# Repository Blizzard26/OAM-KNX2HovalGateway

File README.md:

# Hoval2KNXGateway

A KNX gateway for Hoval TopTronic systems, enabling integration between KNX home automation networks and Hoval CAN-based controllers.

It is a PlatformIO project and needs a working ETS 5.7 (or higher) installed on the same PC (at least for generating the required ETS files).

It uses some Modules from the OpenKNX project: OGM-Common, OFM-cnofigTransfer, OFM-FileTransferModule, OFM-LogicModule

## Description

This project implements a bridge between KNX protocol and Hoval's proprietary CAN-based communication protocol. It allows KNX devices to read and write parameters from Hoval TopTronic systems.

The gateway uses the Hoval Message Protocol over CAN bus at 50kbps, supporting both single and multi-part messages for comprehensive datapoint access.

## Supported Hardware

Currently supports

- Seeeduino XIAO RP2040 with a MCP2515 (and a support CAN Transceive, e.g. MCP2562). Make sure to electrically separate the KNX bus from the Hoval bus as the operate on different potentials.

## Software Requirements

- **PlatformIO**: For building and flashing the firmware
- **Git**: For cloning this repository
- **Arduino Framework**: Used via PlatformIO
- **Dependencies**:
  - KNX library (version 2.2.2+)
  - Seeed Arduino CAN library
  - Various OpenKNX modules

## Installation

1. Clone this repository and initialize submodules:
   ```bash
   git clone <repository-url>
   cd Hoval2KNXGateway
   git submodule update --init --recursive
   ```
   NOTE: In contrast to other OpenKNX Projects this project uses git submodule to pull in libraries instead of restore scripts and `dependencies.txt`.

2. Install PlatformIO if not already installed.

3. Install dependencies:
   ```bash
   pio lib install
   ```

## Building

Use the provided build scripts or PlatformIO directly:

### Development Build
```bash
scripts/Build-Release.ps1
```
Or use the VS Code task: `Build-Dev`

### Release Build
```bash
scripts/Build-Release.ps1 Release
```
Or use the VS Code task: `Build-Release`

### Configuration

- Configure KNX parameters using ETS (Engineering Tool Software)

### Monitoring

Connect to the serial port at 115200 baud for debug output and monitoring.

There are four new commands added:

- `hoval log message`: Log received and processed messages - header only.
- `hoval log messageData`: Log received and processed message - including (parsed) data.
- `hoval log filtered`: Log filtered message, i.e., messages not known to the decoder - header only.
- `hoval log filteredData`: Log filtered message - including raw data.

## Project Structure

- `src/`: Main source code
- `include/`: Header files and configuration
- `lib/`: Library dependencies and modules
- `docs/`: Protocol documentation (Hoval.adoc)
- `schematics/`: Hardware schematics in KiCad format
- `scripts/`: Build and utility scripts
- `test/`: Test files

## Documentation

Detailed protocol documentation is available in `docs/Hoval.adoc`, including:
- Message structure and addressing
- Function codes and datapoints
- Communication flow examples

## Contributing

1. Fork the repository
2. Create a feature branch
3. Make your changes
4. Test thoroughly
5. Submit a pull request

## License

GNU General Public License v3.0

## Support

For issues and questions:
- Check the debug logs via serial output
- Refer to the protocol documentation
- Ensure proper hardware connections

## Disclaimer

This software is provided as-is. Ensure compatibility with your specific Hoval system and KNX installation. Always backup configurations before making changes.

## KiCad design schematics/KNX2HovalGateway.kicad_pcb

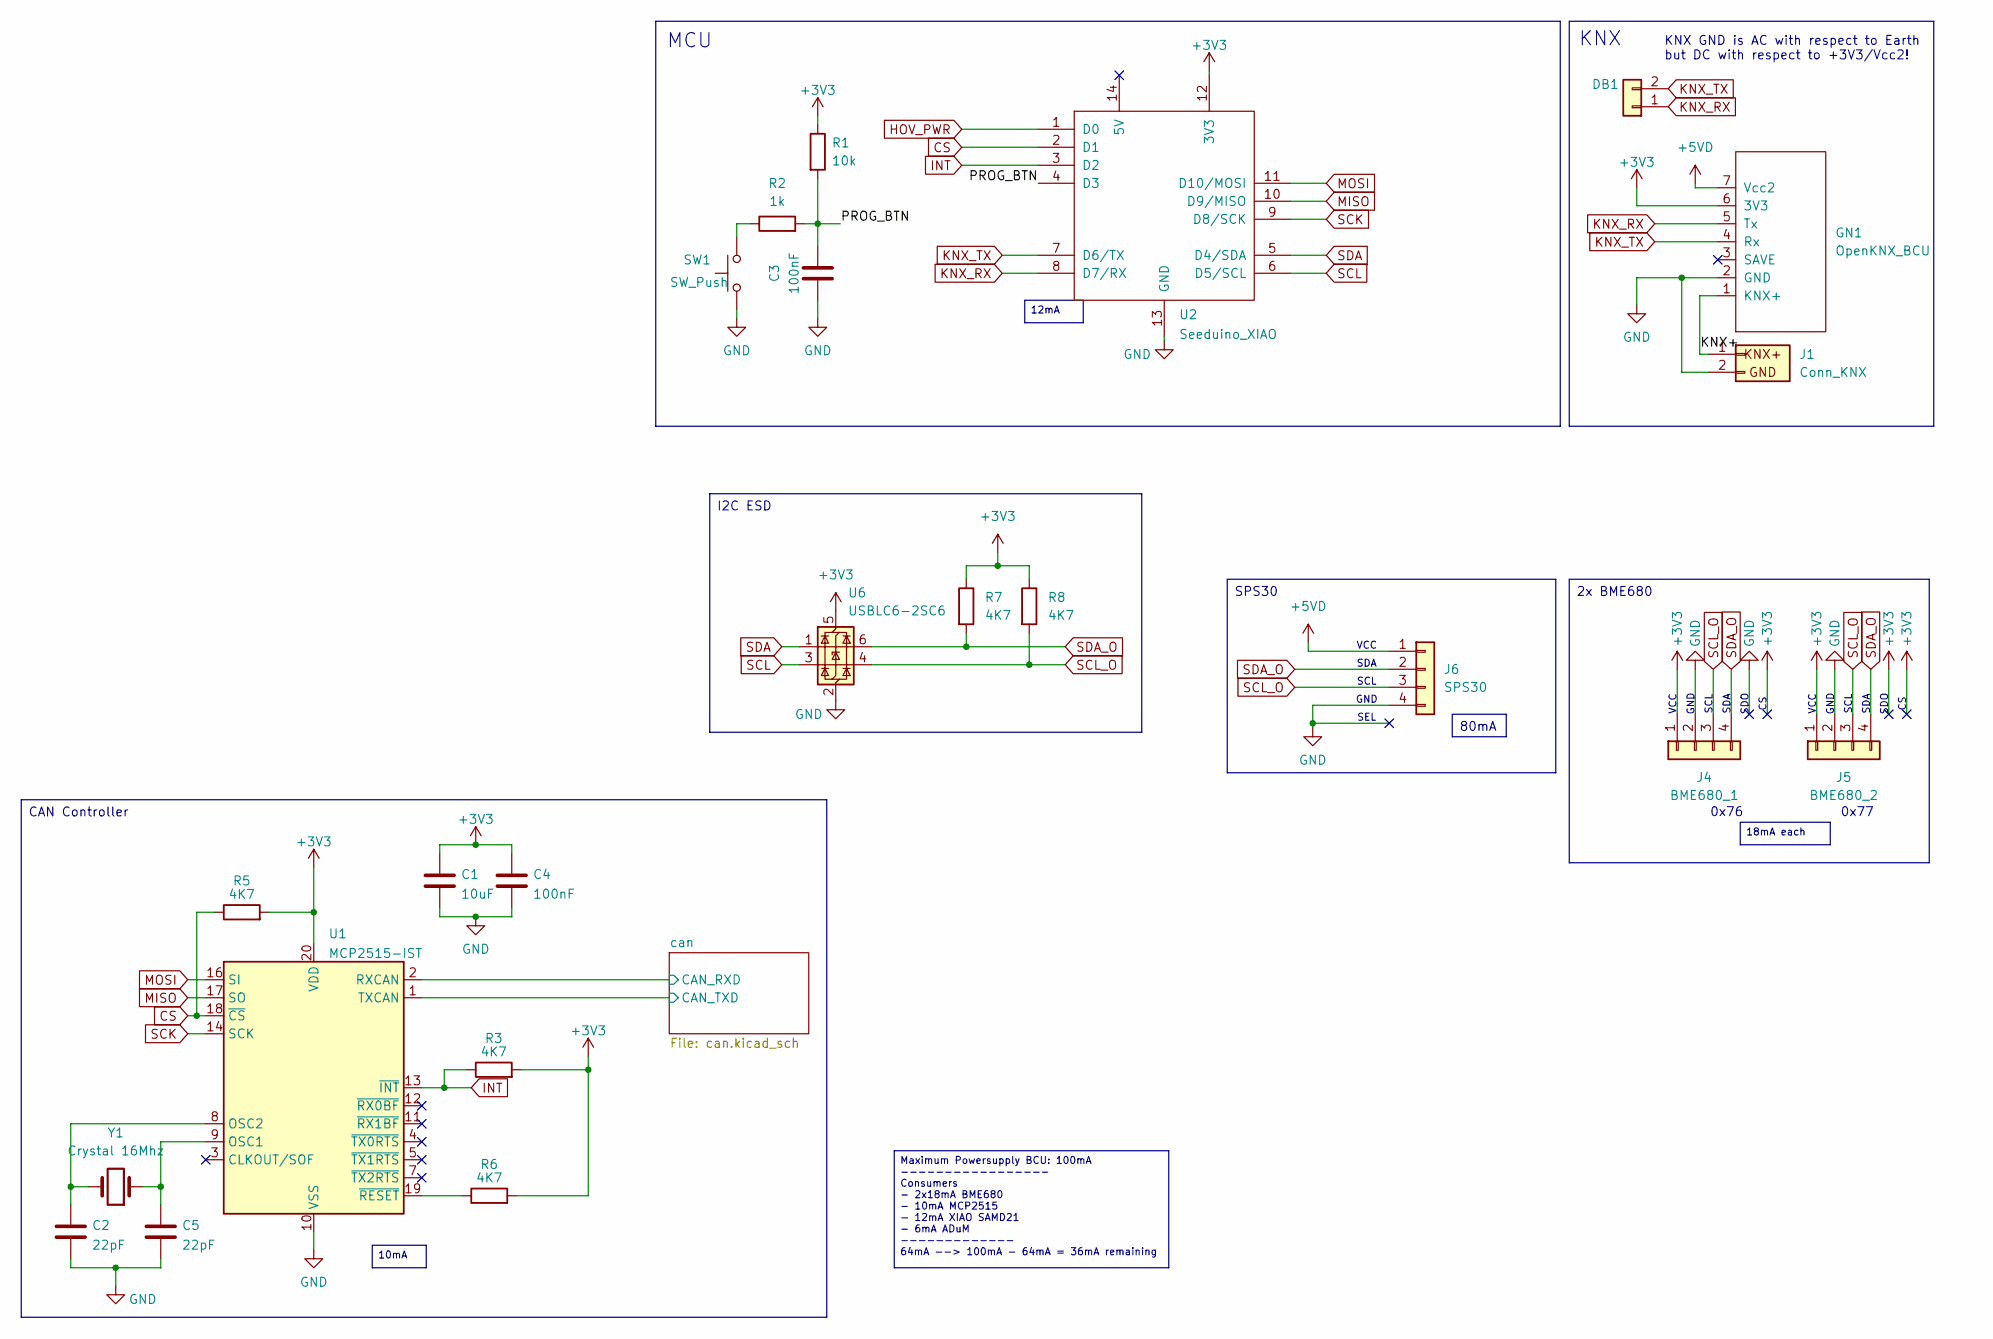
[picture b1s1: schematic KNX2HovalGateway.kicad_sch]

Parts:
C1: 10uF; C_0603_1608Metric_Pad1.08x0.95mm_HandSolder
C2, C5: 22pF; C_0603_1608Metric_Pad1.08x0.95mm_HandSolder
C3, C4: 100nF; C_0603_1608Metric_Pad1.08x0.95mm_HandSolder
DB1: Conn_01x02; PinHeader_1x02_P2.54mm_Vertical
GN1: OpenKNX_BCU; NanoBCU_Soldered
J1: Conn_KNX; KNX_Connector
J4: BME680_1; Molex_SL_171971-0004_1x04_P2.54mm_Vertical
J5: BME680_2; Molex_SL_171971-0004_1x04_P2.54mm_Vertical
J6: SPS30; Molex_SL_171971-0004_1x04_P2.54mm_Vertical
R1: 10k; R_0603_1608Metric_Pad0.98x0.95mm_HandSolder
R2: 1k; R_0603_1608Metric_Pad0.98x0.95mm_HandSolder
R3, R5, R6, R7, R8: 4K7; R_0603_1608Metric_Pad0.98x0.95mm_HandSolder
SW1: SW_Push; B3FS-1000
U1: MCP2515-IST; TSSOP-20_4.4x6.5mm_P0.65mm
U2: Seeduino_XIAO; XIAO-RP2040-DIP
U6: USBLC6-2SC6; SOT-23-6
Y1: Crystal 16Mhz; Crystal_SMD_5032-2Pin_5.0x3.2mm_HandSoldering

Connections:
+3V3: C1.1, C4.1, GN1.6 (3V3), J4.1, J5.1, R1.1, R3.2, R5.2, R6.2, R7.1, R8.1, U1.20 (VDD), U2.12 (3V3), U6.5 (VBUS); also elsewhere on the board
+5VD: GN1.7 (Vcc2), J6.1
/KNX+: GN1.1 (KNX+), J1.1
/PROG_BTN: C3.2, R1.2, R2.2, U2.4 (D3)
/can/CAN_RXD: U1.2 (RXCAN); also elsewhere on the board
/can/CAN_TXD: U1.1 (TXCAN); also elsewhere on the board
CS: R5.1, U1.18 (~CS), U2.2 (D1)
GND: C1.2, C2.2, C3.1, C4.2, C5.2, GN1.2 (GND), J1.2, J4.2, J5.2, J6.4, SW1.1, U1.10 (VSS), U2.13 (GND), U6.2 (GND); also elsewhere on the board
HOV_PWR: U2.1 (D0); also elsewhere on the board
INT: R3.1, U1.13 (~INT), U2.3 (D2)
KNX_RX: DB1.1, GN1.5 (Tx), U2.8 (D7/RX)
KNX_TX: DB1.2, GN1.4 (Rx), U2.7 (D6/TX)
MISO: U1.17 (SO), U2.10 (D9/MISO)
MOSI: U1.16 (SI), U2.11 (D10/MOSI)
unnamed: R2.1, SW1.2
unnamed: C5.1, U1.9 (OSC1), Y1.1
unnamed: C2.1, U1.8 (OSC2), Y1.2
unnamed: R6.1, U1.19 (~RESET)
SCK: U1.14 (SCK), U2.9 (D8/SCK)
SCL: U2.6 (D5/SCL), U6.3 (I/O2)
SCL_O: J4.3, J5.3, J6.3, R8.2, U6.4 (I/O2)
SDA: U2.5 (D4/SDA), U6.1 (I/O1)
SDA_O: J4.4, J5.4, J6.2, R7.2, U6.6 (I/O1)

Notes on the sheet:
SCL
SDO
SDA
0x76
GND
0x77
VCC
KNX
SEL
KNX GND is AC with respect to Earth but DC with respect to +3V3/Vcc2!
I2C ESD
SPS30
2x BME680
CAN Controller
80mA
18mA each
12mA
Maximum Powersupply BCU: 100mA ----------------- Consumers - 2x18mA BME680 - 10mA MCP2515 - 12mA XIAO SAMD21 - 6mA ADuM ------------- 64mA --> 100mA - 64mA = 36mA remaining
MCU
10mA

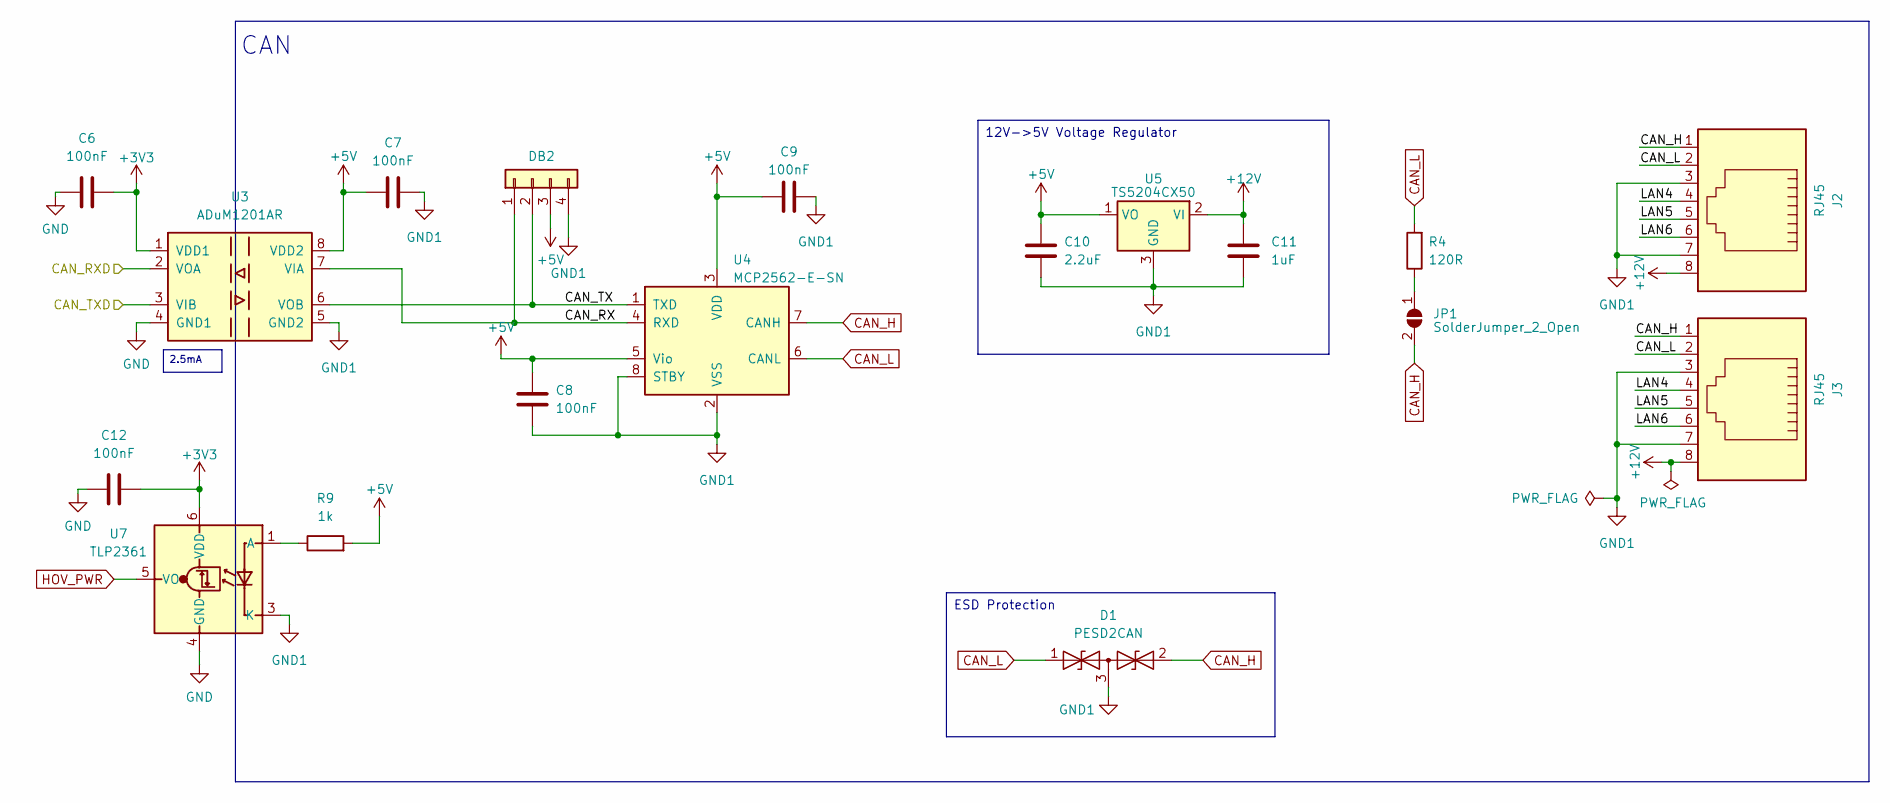
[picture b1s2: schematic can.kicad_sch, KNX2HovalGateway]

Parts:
C6, C7, C8, C9, C12: 100nF; C_0603_1608Metric_Pad1.08x0.95mm_HandSolder
C10: 2.2uF; C_0603_1608Metric_Pad1.08x0.95mm_HandSolder
C11: 1uF; C_0603_1608Metric_Pad1.08x0.95mm_HandSolder
D1: PESD2CAN; SOT-23
DB2: Conn_01x02; PinHeader_1x04_P2.54mm_Vertical
J2, J3: RJ45; RJ45_Ninigi_GE
JP1: SolderJumper_2_Open; SolderBridge
R4: 120R; R_0603_1608Metric_Pad0.98x0.95mm_HandSolder
R9: 1k; R_0603_1608Metric_Pad0.98x0.95mm_HandSolder
U3: ADuM1201AR; SOIC-8_3.9x4.9mm_P1.27mm
U4: MCP2562-E-SN; SOIC-8_3.9x4.9mm_P1.27mm
U5: TS5204CX50; SOT-23-3
U7: TLP2361; Toshiba_SOIC-5-6_4.4x3.6mm_P1.27mm

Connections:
+3V3: C6.2, C12.2, U3.1 (VDD1), U7.6 (VDD); also elsewhere on the board
+5V: C7.1, C8.2, C9.1, C10.1, DB2.3, R9.2, U3.8 (VDD2), U4.3 (VDD), U4.5 (Vio), U5.1 (VO)
+12V: C11.1, J2.8, J3.8, U5.2 (VI)
/can/CAN_RX: DB2.1, U3.7 (VIA), U4.4 (RXD)
/can/CAN_RXD: U3.2 (VOA); also elsewhere on the board
/can/CAN_TX: DB2.2, U3.6 (VOB), U4.1 (TXD)
/can/CAN_TXD: U3.3 (VIB); also elsewhere on the board
/can/LAN4: J2.4, J3.4
/can/LAN5: J2.5, J3.5
/can/LAN6: J2.6, J3.6
CAN_H: D1.2 (A2), J2.1, J3.1, JP1.2 (B), U4.7 (CANH)
CAN_L: D1.1 (A1), J2.2, J3.2, R4.2, U4.6 (CANL)
GND: C6.1, C12.1, U3.4 (GND1), U7.4 (GND); also elsewhere on the board
GND1: C7.2, C8.1, C9.2, C10.2, C11.2, D1.3 (common), DB2.4, J2.3, J2.7, J3.3, J3.7, U3.5 (GND2), U4.2 (VSS), U4.8 (STBY), U5.3 (GND), U7.3 (K)
HOV_PWR: U7.5 (VO); also elsewhere on the board
unnamed: JP1.1 (A), R4.1
unnamed: R9.1, U7.1 (A)

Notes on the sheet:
CAN
ESD Protection
2.5mA
12V->5V Voltage Regulator

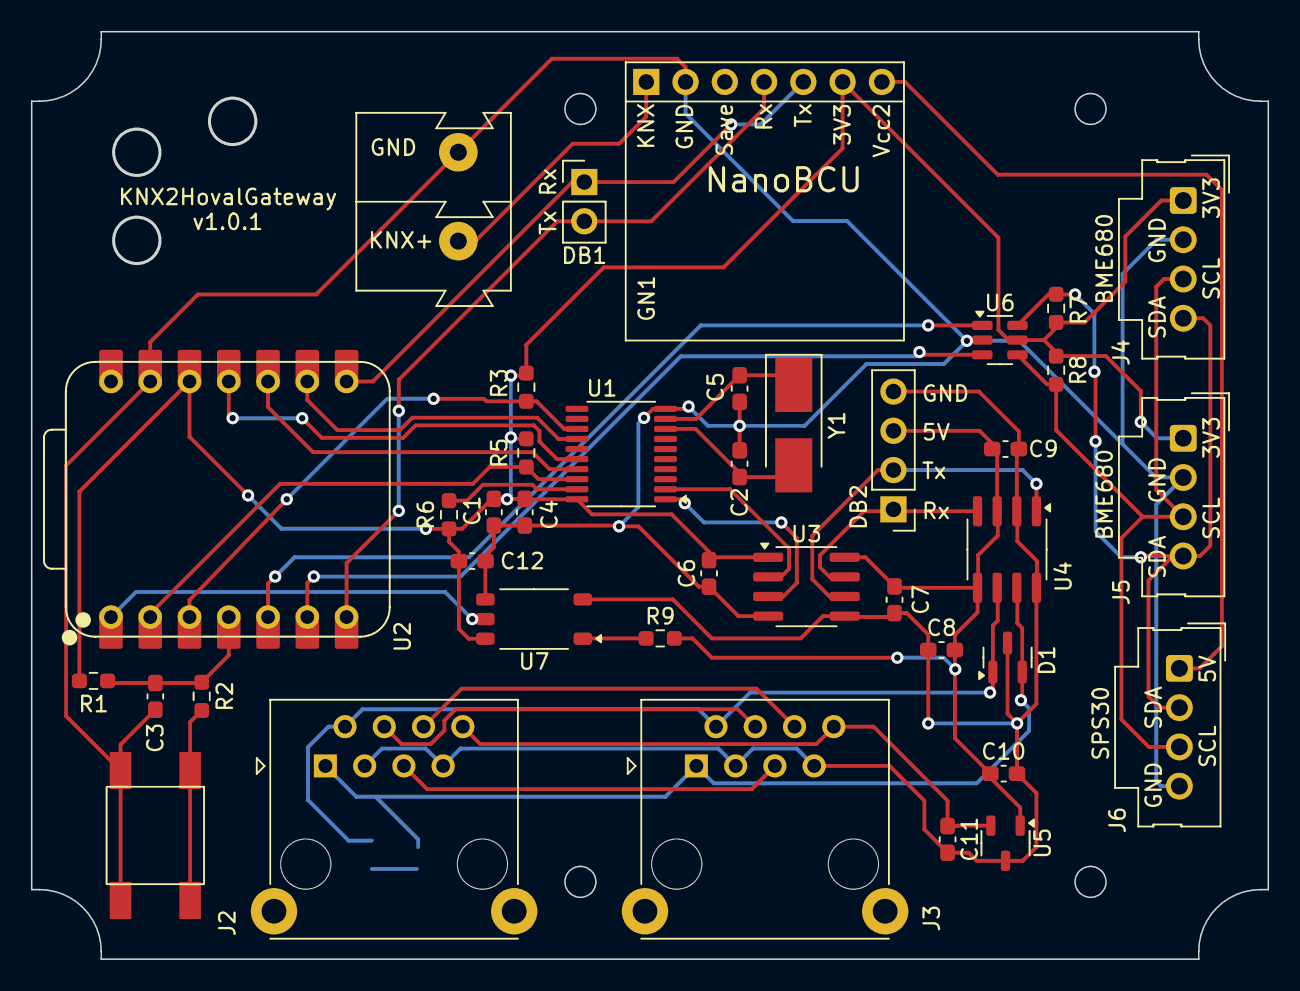
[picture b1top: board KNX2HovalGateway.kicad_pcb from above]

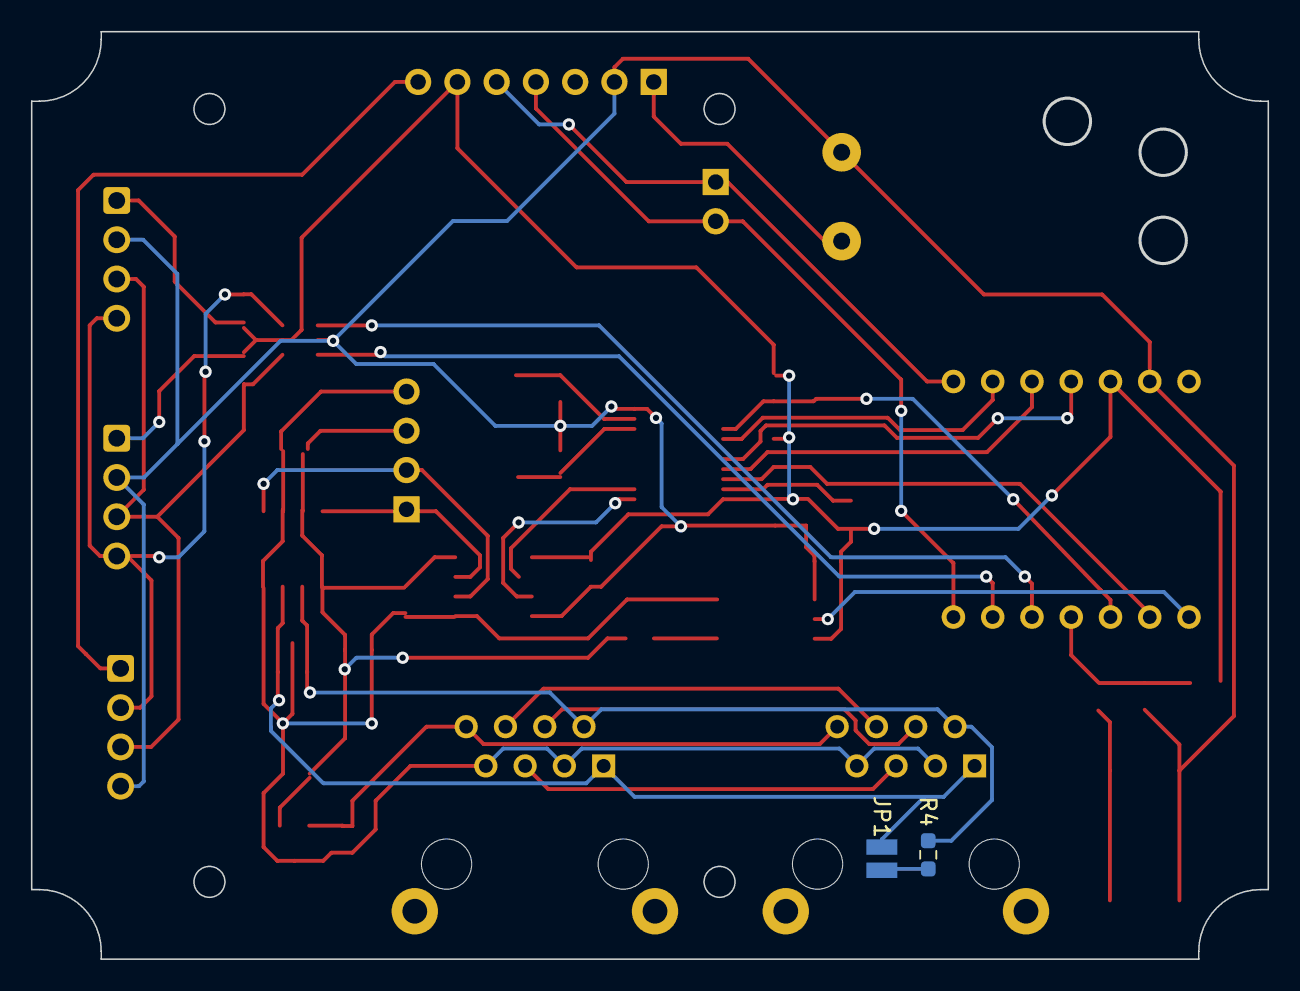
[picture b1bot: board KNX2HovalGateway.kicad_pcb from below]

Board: 2 copper layers, 80.0 x 60.0 mm, 41 parts (2 on the bottom side), 35 nets.

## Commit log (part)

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2026-04-08 Add analysis and description of Hoval Protocol
    This reverts commit 00ff4016ebb15c968af8bb68b50861c8e50a1ba1.
2026-04-08 Empty PIO Project
2026-04-08 Add Schematics for KNX2HovalGateway
2026-04-08 KNX2HovalGateway inital implementation
2026-04-08 Add Readme.md (generated with GitHub Copilot)
2026-04-10 Remove unnecessary logging of loop-times
2026-04-10 Switch to simple loop
2026-04-10 Replace ifndef by pragma once
2026-04-10 Remove unnecessary logging in setup
2026-04-10 Updating dependencies
    knx @ V2.3.1
    OFM-ConfigTransfer @ 0.5.0
    OFM-FileTransferModule @ 3a96b4e
    OFM-LogicModule @ 5672e4f
    OGM-Common @ v1.7.2
2026-04-10 Fix Overlapping Unions
2026-04-10 Change Abbreviation to HOV
2026-04-11 Add Diagnose KO
2026-04-12 Use IndentLevel for indentation
2026-04-12 Remove unnecessary delayCheck define
2026-04-14 Add Icons
2026-04-14 Rename Parameters
2026-04-14 Add dependencies.txt
2026-04-14 Version 0.3.0
2026-05-03 Align platformio.ini
2026-05-26 Make function pointers const
2026-05-26 Some code improvements and cleanup
2026-05-26 Improve Processing of error messages
